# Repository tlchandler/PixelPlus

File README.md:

# PixelPlus

**A modern show player for Raspberry Pi pixel controllers.** PixelPlus plays the
Christmas (or any) light shows you design in [xLights](https://github.com/xLightsSequencer/xLights),
on Raspberry Pi based differential pixel controllers — with an interface built around your
**props**, not channels and universes.

It is a from-scratch replacement for Falcon Player (FPP) for the PixelPlus / Chandler board
family (difftx pHAT, 60-port difftxlarge, diffsmart smart receiver), and also runs on a bare
Pi or in Docker as a show director.

---

## Why PixelPlus

| | |
|---|---|
| **Props, not universes** | Import your xLights layout and every prop shows up by name, wired to its controller, jack, receiver and port — in plain language ("Main Controller › J1 › Front Yard receiver › Port 2 › pixels 51–100"). You never type a start channel. |
| **Configure once, on the leader** | One Pi is the show leader. New controllers appear on their own; click **Adopt** and they receive their props, settings and their slice of every sequence automatically — and stay in sync to within a frame. |
| **Easy to change** | Every setting is edited in place and saved automatically, with Undo. Every change is versioned; **Backups** restore the whole show in one click. |
| **Setup that just works** | Put your Wi-Fi in `pixelplus.txt` on the SD card, use Raspberry Pi Imager's settings, or use the **PixelPlus Imager** app. No Wi-Fi? The Pi opens a `PixelPlus-XXXX` hotspot with a friendly Wi-Fi picker. |
| **Made for the yard at night** | Dark "studio" interface that works beautifully on a phone: big touch targets, live preview of your whole display, test and fault-find any prop from where you stand. |
| **No artificial limits** | Up to ~1600 pixels per output at 20 fps (800 at 40 fps) on every output, 60 outputs on the difftxlarge. |

## Features

- **Live dashboard** — now playing, next show countdown, pre-show health check, controller
  health, temperatures, 12 V voltage/current (difftxlarge), song requests.
- **Props** — grid and list views with live mini-previews, groups, bulk edit, drag-to-reorder
  daisy chains, reverse runs, dark spacer pixels, color order, brightness and color correction
  per port, power estimates against your receiver fuses.
- **Test & fault finder** — solid/chase/count/walk patterns on any prop or port; a guided
  "is it lit?" binary search finds the first bad pixel in a handful of taps.
- **Layout** — a live 2D picture of your whole display while the show plays.
- **Sequences & audio** — drag-and-drop upload, automatic song matching, volume leveling,
  thumbnails; plays xLights `.fseq` v1/v2 (zstd, zlib, sparse).
- **Playlists** — songs, DJ clips, looks, pauses and commands; intro/outro, shuffle, repeat,
  crossfades.
- **Schedule** — show windows by day and season, times relative to sunset, special nights
  that take over, idle looks between shows, a neighbor-friendly volume curfew.
- **DJ Studio** — radio-style announcements with Kokoro voices (Nick & Holly included, or
  blend your own), multi-voice scripts, hype levels, live info ("{days until Christmas}",
  "next up: {song}") re-rendered at showtime. Renders on a Pi 4/5 or right in your browser.
- **Effects** — 13 built-in effects and 15 ready-made looks for idle time and quick tests,
  identical on every controller.
- **Games** — visitors play Super Mario Bros. (or an NES arcade) on your pixel matrix using
  their phone as the controller, with QR invites flashed on the matrix.
- **Song requests** — a public page (with QR code and printable yard sign) where visitors pick
  the next song.
- **Alerts & integrations** — email and push (ntfy) alerts, MQTT with Home Assistant
  discovery, physical button triggers, OLED status screen.
- **Only what you use** — Settings → Features turns optional parts on and off (presets:
  Essentials, Everything, Custom), so menus and pages show just what this display uses.
  Nothing is deleted; turned-off features stop their background work and their playlist items
  are skipped.
- **Secure by default** — optional password, per-controller keys with signed cluster
  traffic, hardened against hostile uploads and cross-site attacks.

**New in this release**

- **Light shows from music** — beat, tempo and energy analysis builds a show for your props
  in one click, in six styles; preview any sequence on your phone without touching the lights.
- **Sync lights to sound** — your phone's camera and microphone measure the audio delay; a
  built-in certificate authority gives phones the HTTPS they need, with a one-page trust guide.
- **Countdown to showtime** — a matrix countdown with the first song starting exactly on the
  scheduled minute, on every controller.
- **Map my yard** — film the house with your phone and PixelPlus finds where each prop is and
  which runs are swapped or reversed; plus a pixel-count check and a guided receiver wizard.
- **Smart playlists** — tags, rules and nightly rotation pick tonight's songs without repeats.
- **Seasons** — keep Halloween and Christmas shows side by side and switch by date.
- **Power limiter** — keeps every fuse and supply within its rating on every controller, plus
  late-night dimming.
- **Nightly report** — how last night went, every morning, by email or push.
- **Upload from xLights** — FPP Connect compatible, or a drop folder.
- **Sensors and surprises** — ESP32 motion, button and beam sensors set off effects layered
  over the song that's playing.
- **Remote access** — Tailscale or Cloudflare Tunnel without port forwarding; only the request
  page and games go public, with per-visitor limits and an alert on every remote sign-in.
- **Fleet care** — signed updates for every controller at once with automatic rollback, and
  one-step replacement of a dead controller or leader from an encrypted transfer file.

## Getting started

1. **Make an SD card** — see [docs/INSTALL.md](docs/INSTALL.md) (PixelPlus Imager,
   Raspberry Pi Imager, or any writer + `pixelplus.txt`).
2. **Open** `http://pixelplus.local` (or the name you chose) and follow the setup wizard.
3. **Import** your xLights layout, **upload** sequences, **build** a playlist and **schedule** it.

Running the leader on a PC or NAS: see [docker/README.md](docker/README.md).

## Hardware

| Board | Outputs | Notes |
|---|---|---|
| **difftx** (PixelPlus pHAT) | 4 on one RJ45 | Pi Zero 2 W outline. Rev D needs a 4/5-swapped patch lead on port 3 (PixelPlus warns you). |
| **difftxlarge** | 60 on 15 RJ45 | 3 latch banks, INA226 power monitor, 2× LM75, DS3231 RTC, optional OLED. |
| **diffsmart** | 4 direct | Runs PixelPlus in standalone (PI) mode; set SW1 to **PI**. |
| **diffrx** | receiver | Passive 4-port differential receiver (no Pi). |

Supported Pis: Zero 2 W, 3, 4, 5 (64-bit Raspberry Pi OS Bookworm or Trixie). Pixel output
uses the Pi's DPI peripheral with an original WS281x encoder — see
[crates/pixelplus-output/DESIGN.md](crates/pixelplus-output/DESIGN.md), including a
**bring-up checklist** for first hardware tests.

## Repository layout

```
crates/pixelplus-core     show model, fseq, xLights import, mapping, effects, schedule
crates/pixelplus-output   DPI WS281x encoder (direct + latched), output backends
crates/pixelplus-hw       board detection, EEPROM, sensors, RTC, OLED, GPIO
crates/pixelplus-daemon   pixelplusd: API, playback engine, scheduler, cluster, services
crates/pixelplus-cli      pixelplus: detect, eeprom, test-output, config-txt, doctor
web/                      SvelteKit web interface (demo mode: add ?mock=1)
tts/                      Kokoro DJ voice service
games/                    phone-controlled matrix games
image/ packaging/ docker/ Raspberry Pi image, Debian package, Docker
imager/                   PixelPlus Imager desktop app
docs/                     ARCHITECTURE, INSTALL, BUILDING
scripts/                  dev-cluster.sh (local leader + 2 followers), e2e tests
```

## Development

See [docs/BUILDING.md](docs/BUILDING.md). Quick start:

```sh
cargo test --workspace                  # Rust
cd web && pnpm install && pnpm dev      # UI (demo mode when no daemon is running)
scripts/dev-cluster.sh start --fresh    # a real leader + 2 followers on your PC
node scripts/e2e/run.mjs                # the full end-to-end scenario
```

The design authority is [docs/ARCHITECTURE.md](docs/ARCHITECTURE.md) (multi-controller timing:
§7.4); board-level timing notes for future hardware revisions are in
[docs/HARDWARE-NOTES.md](docs/HARDWARE-NOTES.md).

## License

PixelPlus is free software under the [GNU General Public License v3.0 or later](LICENSE).
It contains no code from FPP's CC-BY-ND licensed components.
Nintendo and Super Mario Bros. are trademarks of Nintendo; no Nintendo code or ROMs are included.

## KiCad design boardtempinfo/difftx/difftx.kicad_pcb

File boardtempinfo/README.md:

# Christmas PCBs

Each design has its own folder. The top of each folder is the current working copy (open the
`.kicad_pro` there); earlier revisions are frozen under `archive/`.

## Tools

All designs are developed in **KiCad 10.0**, installed at `C:\Program Files\KiCad\10.0\`:

| Binary | Path | Used for |
|---|---|---|
| KiCad | `C:\Program Files\KiCad\10.0\bin\kicad.exe` | opening the projects |
| kicad-cli | `C:\Program Files\KiCad\10.0\bin\kicad-cli.exe` | ERC/DRC, gerber and render export |
| KiCad Python | `C:\Program Files\KiCad\10.0\bin\python.exe` | running the `gen_*.py`, `export_jlc.py`, `verify.py` etc. scripts |

The scripts need KiCad's bundled Python (it provides `pcbnew`), so run them from the design's folder, e.g.

```
"C:\Program Files\KiCad\10.0\bin\python.exe" gen_pcb.py
```

## Designs

| Folder | Board | Current | Archived revisions |
|---|---|---|---|
| `difftx/` | FPP Remote pHAT — RS-422 transmitter on the Pi Zero 2 W outline | rev E (65 x 30 mm). Rev D, the one built, has port 3 reversed: see `CLAUDE.md` | `archive/revA`, `archive/revB`, `archive/revC_66mm`, `archive/revD` |
| `diffrx/` | Chandler 4D/8P Differential Receiver | work after rev C (board and `grid_router.py` changed since the release) | `archive/revB`, `archive/revC_release` |
| `diffsmart/` | Chandler 4D/8P Smart Receiver — diffrx rev C + Pi header, RX/TX mode switch | v1.00 | — |
| `difftxlarge/` | 60-output FPP transmitter — 15 × RJ45 (Falcon differential), 3 latch banks, RTC, power monitor, fan thermostat, line out | rev A (310 × 206 mm, not yet ordered) | — |

Each design's `VERIFICATION.md` has its check record; `jlcpcb/` holds the gerbers, BOM and CPL for ordering.

`repoint_3d_models.py` fixes 3D model paths that point at folders that no longer exist (the parts were first
downloaded under `Documents/jumperless/...`), repointing them at each design's own `jlc/jlc.3dshapes`. Run it
with `--apply`; without it, it only reports.

`_duplicates/` holds files that were byte-identical copies of `difftx/archive/revB` files left at the
top level (`fab/`, `difftx_pcb.pdf`). Safe to delete.

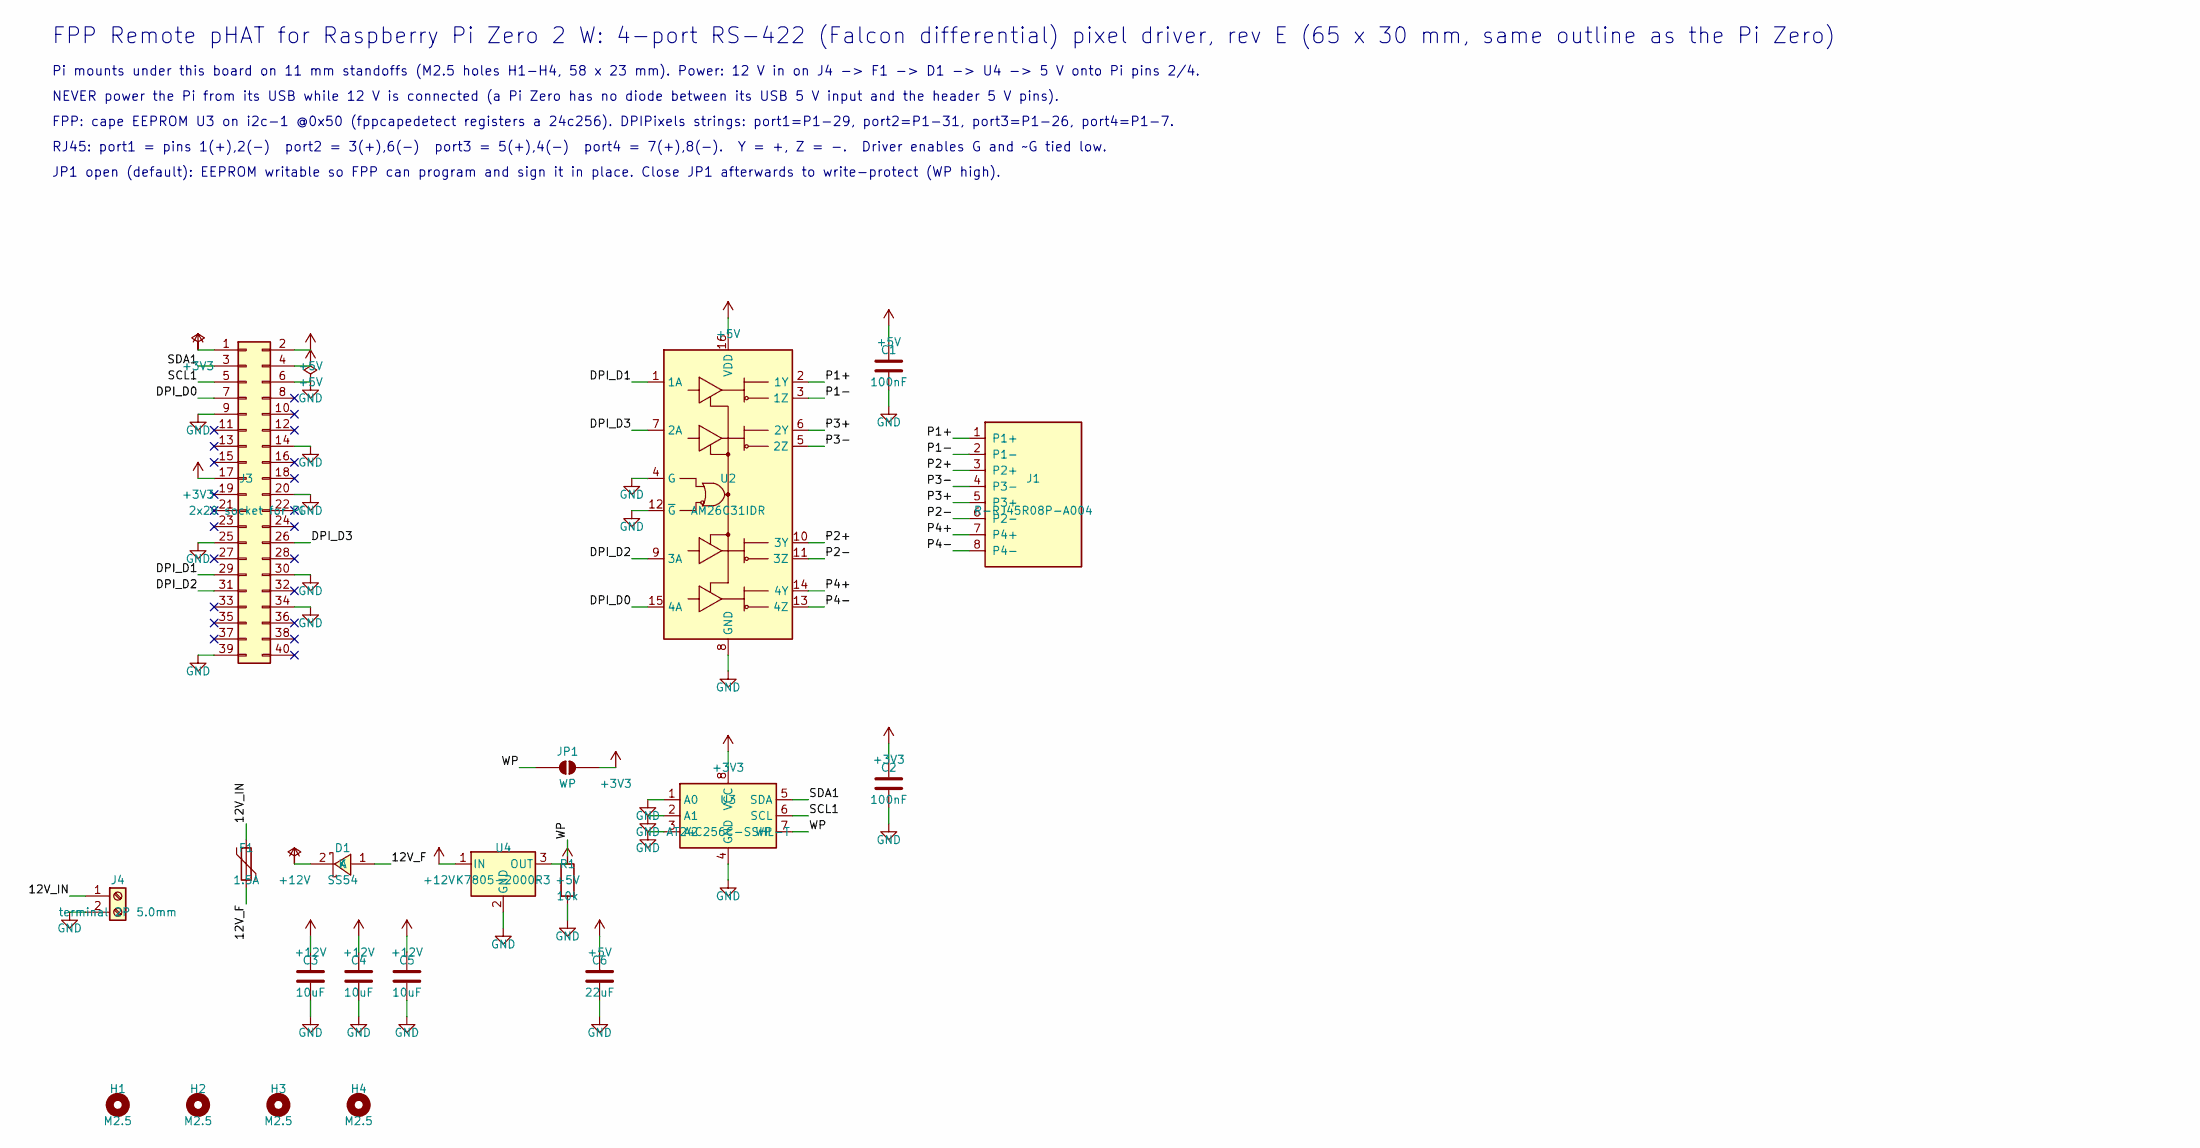
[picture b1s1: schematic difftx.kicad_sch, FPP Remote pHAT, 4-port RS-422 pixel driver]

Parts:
C1, C2: 100nF; C_0805_2012Metric_Pad1.18x1.45mm_HandSolder; LCSC C49678
C3, C4, C5: 10uF; C_1206_3216Metric; LCSC C89632
C6: 22uF; C_0805_2012Metric_Pad1.18x1.45mm_HandSolder; LCSC C45783
D1: SS54; SMA_L4.4-W2.8-LS5.4-R-RD; LCSC C22452
F1: 1.5A; F1812; LCSC C22392774
H1, H2, H3, H4: M2.5; MountingHole_2.7mm_M2.5
J1: R-RJ45R08P-A004; RJ45-TH_R-RJ45R08P-A004; LCSC C385834
J3: 2x20 socket for Pi; PiSocket_2x20_bottom; LCSC C5124634
J4: terminal 2P 5.0mm; CONN-TH_P5.00_KF301-5.0-2P; LCSC C474881
JP1: WP; SolderJumper-2_P1.3mm_Open_Pad1.0x1.5mm
R1: 10k; R_0603_1608Metric; LCSC C25804
U2: AM26C31IDR; SOIC-16_L9.9-W3.9-P1.27-LS6.0-BL; LCSC C34923
U3: AT24C256C-SSHL-T; SOIC-8_L4.9-W3.9-P1.27-LS6.0-BL; LCSC C6482
U4: K7805-2000R3; PWRM-TH_K78XX-2000R3; LCSC C18212380

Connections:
+3V3: C2.1, J3.1, J3.17, JP1.2 (B), U3.8 (VCC)
+5V: C1.1, C6.1, J3.2, J3.4, U2.16 (VDD), U4.3 (OUT)
+12V: C3.1, C4.1, C5.1, D1.2 (K), U4.1 (IN)
/12V_F: D1.1 (A), F1.2
/12V_IN: F1.1, J4.1
/DPI_D0: J3.7, U2.15 (4A)
/DPI_D1: J3.29, U2.1 (1A)
/DPI_D2: J3.31, U2.9 (3A)
/DPI_D3: J3.26, U2.7 (2A)
/P1+: J1.1 (P1+), U2.2 (1Y)
/P1-: J1.2 (P1-), U2.3 (1Z)
/P2+: J1.3 (P2+), U2.10 (3Y)
/P2-: J1.6 (P2-), U2.11 (3Z)
/P3+: J1.5 (P3+), U2.6 (2Y)
/P3-: J1.4 (P3-), U2.5 (2Z)
/P4+: J1.7 (P4+), U2.14 (4Y)
/P4-: J1.8 (P4-), U2.13 (4Z)
/SCL1: J3.5, U3.6 (SCL)
/SDA1: J3.3, U3.5 (SDA)
/WP: JP1.1 (A), R1.1, U3.7 (WP)
GND: C1.2, C2.2, C3.2, C4.2, C5.2, C6.2, J3.6, J3.9, J3.14, J3.20, J3.25, J3.30, J3.34, J3.39, J4.2, R1.2, U2.4 (G), U2.8 (GND), U2.12 (~G), U3.1 (A0), U3.2 (A1), U3.3 (A2), U3.4 (GND), U4.2 (GND)

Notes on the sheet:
FPP Remote pHAT for Raspberry Pi Zero 2 W: 4-port RS-422 (Falcon differential) pixel driver, rev E (65 x 30 mm, same outline as the Pi Zero)
Pi mounts under this board on 11 mm standoffs (M2.5 holes H1-H4, 58 x 23 mm). Power: 12 V in on J4 -> F1 -> D1 -> U4 -> 5 V onto Pi pins 2/4.
NEVER power the Pi from its USB while 12 V is connected (a Pi Zero has no diode between its USB 5 V input and the header 5 V pins).
FPP: cape EEPROM U3 on i2c-1 @0x50 (fppcapedetect registers a 24c256). DPIPixels strings: port1=P1-29, port2=P1-31, port3=P1-26, port4=P1-7.
RJ45: port1 = pins 1(+),2(-) port2 = 3(+),6(-) port3 = 5(+),4(-) port4 = 7(+),8(-). Y = +, Z = -. Driver enables G and ~G tied low.
JP1 open (default): EEPROM writable so FPP can program and sign it in place. Close JP1 afterwards to write-protect (WP high).

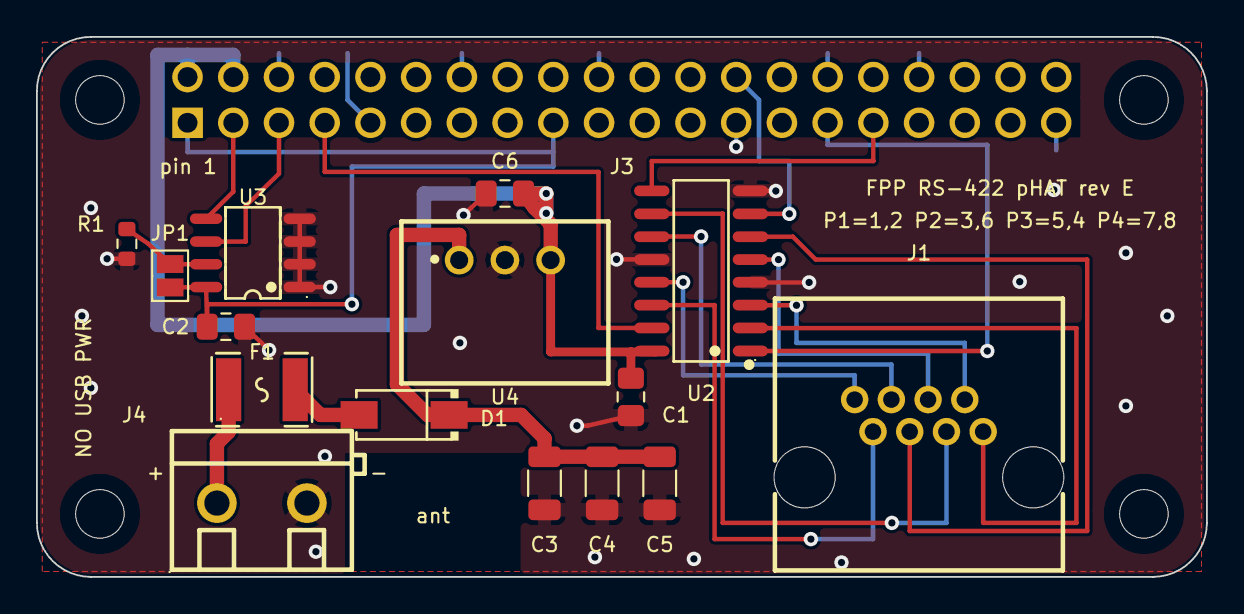
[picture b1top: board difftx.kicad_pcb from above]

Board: 2 copper layers, 65.0 x 30.0 mm, 20 parts (1 on the bottom side), 21 nets.

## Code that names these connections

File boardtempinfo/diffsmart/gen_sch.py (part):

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# ---- cat5 input, termination, fail-safe bias, ESD ---------------------------------------------
PAIR = {1: ("P1P", "P1N"), 2: ("P2P", "P2N"), 3: ("P3P", "P3N"), 4: ("P4P", "P4N")}
place(f"{PROJECT}:RJ45_8P8C", "J14", "R-RJ45R08P-A004", "jlc:RJ45-TH_R-RJ45R08P-A004", 40.64, 76.2, sym_rj, {
    "1": ("label", "P1P"), "2": ("label", "P1N"), "3": ("label", "P2P"), "4": ("label", "P3N"),
    "5": ("label", "P3P"), "6": ("label", "P2N"), "7": ("label", "P4P"), "8": ("label", "P4N"),
}, datasheet="https://www.lcsc.com/datasheet/C385834.pdf",
   descr="RJ45 8P8C jack, right angle, unshielded. Falcon differential pinout (+/-): port1 = 1/2, port2 = 3/6, port3 = 5/4, port4 = 7/8",
   lcsc="C385834")
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# Which receiver channel takes which cat5 pair is a layout choice, not an electrical one: the pairs are
# assigned to whichever channel sits nearest them on the board, and the port number follows the pair.
place(f"{PROJECT}:AM26C32", "U1", "AM26C32IDR", "jlc:SOIC-16_L9.9-W3.9-P1.27-LS6.0-BL", 165.1, 88.9, sym_rx, {
    "2": ("label", "P4P"), "1": ("label", "P4N"), "3": ("label", "RXD4"),
    "6": ("label", "P1P"), "7": ("label", "P1N"), "5": ("label", "RXD1"),
    "10": ("label", "P2P"), "9": ("label", "P2N"), "11": ("label", "RXD2"),
    "14": ("label", "P3P"), "15": ("label", "P3N"), "13": ("label", "RXD3"),
    "4": ("label", "MODE"), "12": ("+5V",), "8": ("GND",), "16": ("+5V",),
}, datasheet="https://www.ti.com/lit/ds/symlink/am26c32.pdf",
   descr="Quad RS-422 differential line receiver, SOIC-16. A = '+', B = '-', Y = H when A-B > 200 mV. ~G is tied high so the enable is G alone: G high = receiving, G low = outputs Hi-Z and the Pi drives instead",
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      datasheet="https://www.lcsc.com/datasheet/C4747956.pdf",
      descr="Bulk capacitor on the 12 V bus (pin 1 = +). Damps the inductance of the run back to the supply", lcsc="C4747956")

res("R3", "10R", 215.9, 236.22, ("+12V",), ("label", "VREG"), "Feeds the regulator through a resistor so a clamped surge cannot slam its 25 V input", "C22859")
cap("C2", "10uF", 241.3, 248.92, ("label", "VREG"), ("GND",), "Regulator input bulk, 10 uF 50 V X5R 1206", "C13585", fp=C1206)
cap("C3", "100nF", 261.62, 248.92, ("label", "VREG"), ("GND",), "Regulator input bypass 100 nF 50 V", "C49678")
place(f"{PROJECT}:UA78M05", "U3", "UA78M05CDCYR", "jlc:SOT-223_L6.5-W3.5-P2.30-LS7.0-BR", 289.56, 236.22, sym_reg,
      {"1": ("label", "VREG"), "2": ("GND",), "3": ("+5V", "flag"), "4": ("GND",)},
      datasheet="https://www.ti.com/lit/ds/symlink/ua78m33c.pdf",
      descr="5 V 500 mA linear regulator, SOT-223 (1 = IN, 2 and tab = GND, 3 = OUT). Load is about 50 mA, so it dissipates under 0.4 W",
      lcsc="C201654")
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# NTCS0805E3103FHT: 10 k at 25 C, B25/85 = 3940 K, so the divider node /NTC falls as the board heats:
#   43 C -> 1.60 V   (fan on)        65 C -> 0.88 V   (alarm)
place(f"{PROJECT}:LM2903", "U6", "LM2903QDRQ1", "jlc:SOIC-8_L4.9-W3.9-P1.27-LS6.0-BL", 330.2, 317.5, sym_cmp,
      {"1": ("label", "FANDRV"), "2": ("label", "NTC"), "3": ("label", "VREFAN"), "4": ("GND",),
       "5": ("label", "NTC"), "6": ("label", "VREFOT"), "7": ("label", "OT"), "8": ("+12V",)},
      datasheet="https://www.lcsc.com/datasheet/C475499.pdf",
      descr="Dual comparator, AEC-Q100 grade 1: half A switches the fan, half B lights the over-temp LED",
      lcsc="C475499")
cap("C9", "100nF", 381.0, 317.5, ("+12V",), ("GND",), "LM2903 decoupling, on the 12 V side", "C49678")
res("R29", "10k",  101.6, 292.1, ("+5V",), ("label", "NTC"), "Top of the NTC divider", "C25804")
place(f"{PROJECT}:R", "RT5", "10k NTC", "Resistor_SMD:R_0805_2012Metric", 101.6, 317.5, sym_r,
      {"1": ("label", "NTC"), "2": ("GND",)},
      datasheet="https://www.lcsc.com/datasheet/C3195213.pdf",
      descr="Board temperature sensor for the fan thermostat: Vishay NTCS0805E3103FHT, 10 k at 25 C, "
            "B25/85 = 3940 K. Placed between the FET bank and the main fuse, the hottest corner",
      lcsc="C3195213")
res("R30", "10k",  152.4, 292.1, ("+5V",), ("label", "VREFAN"), "Fan threshold reference, top", "C25804")
res("R31", "4.7k", 152.4, 317.5, ("label", "VREFAN"), ("GND",), "Fan threshold reference, bottom (1.60 V ~ 43 C)", "C23162")
res("R32", "100k", 203.2, 292.1, ("label", "FANDRV"), ("label", "VREFAN"), "Fan thermostat hysteresis, about 2.4 C", "C25803")
res("R33", "4.7k", 203.2, 317.5, ("+5V",), ("label", "FANDRV"), "Pull-up for the LM2903's open-drain output", "C23162")
res("R34", "4.7k", 254.0, 292.1, ("+5V",), ("label", "VREFOT"), "Over-temp threshold reference, top", "C23162")
res("R35", "1k",   254.0, 317.5, ("label", "VREFOT"), ("GND",), "Over-temp threshold reference, bottom (0.88 V ~ 65 C)", "C21190")
res("R36", "1k",   101.6, 342.9, ("+5V",), ("label", "OTA"), "Over-temp LED series resistor", "C21190")
place(f"{PROJECT}:LED", "LED6", "red", FP_LED, 152.4, 342.9, sym_led,
      {"1": ("label", "OTA"), "2": ("label", "OT")},
      descr="OVER TEMP indicator: lit above about 65 C on the board", lcsc="C2295")

# ---- fan output ---------------------------------------------------------------------------------
# The fan belongs on the enclosure wall blowing across the two fuse rows, not bolted to the board, so
# this is an output and not a mount. Fused on its own so a chafed fan lead cannot lean on the 30 A bus.
res("R37", "100k", 254.0, 342.9, ("label", "FANDRV"), ("GND",),
    "Gate pull-down: the fan stays off if U6 is unpopulated", "C25803")
place(f"{PROJECT}:AO3400A", "Q5", "AO3400A", "jlc:SOT-23-3_L2.9-W1.3-P1.90-LS2.4-BR", 101.6, 368.3, sym_nfet,
      {"1": ("label", "FANDRV"), "2": ("GND",), "3": ("label", "FANM")},
      datasheet="https://www.lcsc.com/datasheet/C20917.pdf",
      descr="Fan low-side switch, 30 V 5.7 A", lcsc="C20917")
place(f"{PROJECT}:Polyfuse", "F13", "0.35A/30V", "Fuse:Fuse_1206_3216Metric", 152.4, 368.3, sym_fuse,
      {"1": ("+12V",), "2": ("label", "FAN12")},
      datasheet="https://www.lcsc.com/datasheet/C2876002.pdf",
      descr="Fan branch fuse: Fuzetec FSMD035-30-1206R, 0.35 A hold / 0.7 A trip, 30 V. Keep the fan "
            "under 200 mA, i.e. 40 or 60 mm, not 80 mm",
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# the freewheel diode is anode-on-switch-node, cathode-on-supply; the other way round it is a forward
# diode across the fan supply every time Q5 turns on.
place(f"{PROJECT}:SS34", "D8", "SS34", "jlc:SMA_L4.3-W2.6-LS5.2-RD", 203.2, 368.3, sym_schk,
      {"1": ("label", "FAN12"), "2": ("label", "FANM")},
      datasheet="https://www.lcsc.com/datasheet/C8678.pdf",
      descr="Flyback across the fan", lcsc="C8678")
place(f"{PROJECT}:Screw_Terminal_01x03", "J16", "FAN 12V", "jlc:CONN-TH_3P-P5.00_KF301-5.0-3P", 266.7, 368.3, sym_t3,
      {"1": ("label", "FAN12"), "2": ("label", "FANM"), "3": ("GND",)},
      descr="Fan output: fused +12 V, switched return, and a spare ground pole. Silk marked + - G",
      lcsc="C474882")

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# there is no master on the board to read them anyway. The fan and the alarm LED do not depend on them.
place(f"{PROJECT}:LM75B", "U4", "LM75BD", "jlc:SOIC-8_L5.0-W4.0-P1.27-LS6.0-BL", 571.5, 38.1, sym_lm75,
      {"1": ("label", "SDA"), "2": ("label", "SCL"), "3": ("NC",), "4": ("GND",),
       "5": ("GND",), "6": ("GND",), "7": ("GND",), "8": ("label", "P3V3")},
      datasheet="https://www.lcsc.com/datasheet/C34565.pdf",
      descr="Hot-corner temperature sensor, I2C address 0x48 (A2/A1/A0 all low). Sits between the FET "
            "bank and the main fuse",
      lcsc="C34565")
cap("C7", "100nF", 622.3, 38.1, ("label", "P3V3"), ("GND",), "U4 decoupling", "C49678")
place(f"{PROJECT}:LM75B", "U5", "LM75BD", "jlc:SOIC-8_L5.0-W4.0-P1.27-LS6.0-BL", 571.5, 88.9, sym_lm75,
      {"1": ("label", "SDA"), "2": ("label", "SCL"), "3": ("NC",), "4": ("GND",),
       "5": ("GND",), "6": ("GND",), "7": ("label", "P3V3"), "8": ("label", "P3V3")},
      datasheet="https://www.lcsc.com/datasheet/C34565.pdf",
      descr="Enclosure-ambient temperature sensor, I2C address 0x49 (A0 high). Placed in the top-left "
            "corner, as far from the power section as the board allows",
      lcsc="C34565")
cap("C8", "100nF", 622.3, 88.9, ("label", "P3V3"), ("GND",), "U5 decoupling", "C49678")
res("R39", "4.7k", 673.1, 38.1, ("label", "P3V3"), ("label", "SDA"), "I2C bus pull-up to 3V3. With a Pi fitted this parallels its own 1.8 k, giving 1.3 k and a 72 ns rise", "C23162")
res("R40", "4.7k", 673.1, 63.5, ("label", "P3V3"), ("label", "SCL"), "I2C bus pull-up to 3V3. With a Pi fitted this parallels its own 1.8 k, giving 1.3 k and a 72 ns rise", "C23162")
place(f"{PROJECT}:Conn_01x04", "J15", "header 1x4", "jlc:HDR-TH_4P-P2.54-V-M", 723.9, 63.5, sym_hdr,
      {"1": ("GND",), "2": ("label", "P3V3"), "3": ("label", "SDA"), "4": ("label", "SCL")},
      descr="I2C breakout: GND / 3V3 / SDA / SCL. 3.3 V ONLY, in either direction - a Pi fitted in the "
            "socket drives this pin, and SDA/SCL are hard-wired to its GPIO2 and GPIO3, which are not "
            "5 V tolerant. Feed it 3.3 V from an external master "
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      lcsc="C124378")
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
